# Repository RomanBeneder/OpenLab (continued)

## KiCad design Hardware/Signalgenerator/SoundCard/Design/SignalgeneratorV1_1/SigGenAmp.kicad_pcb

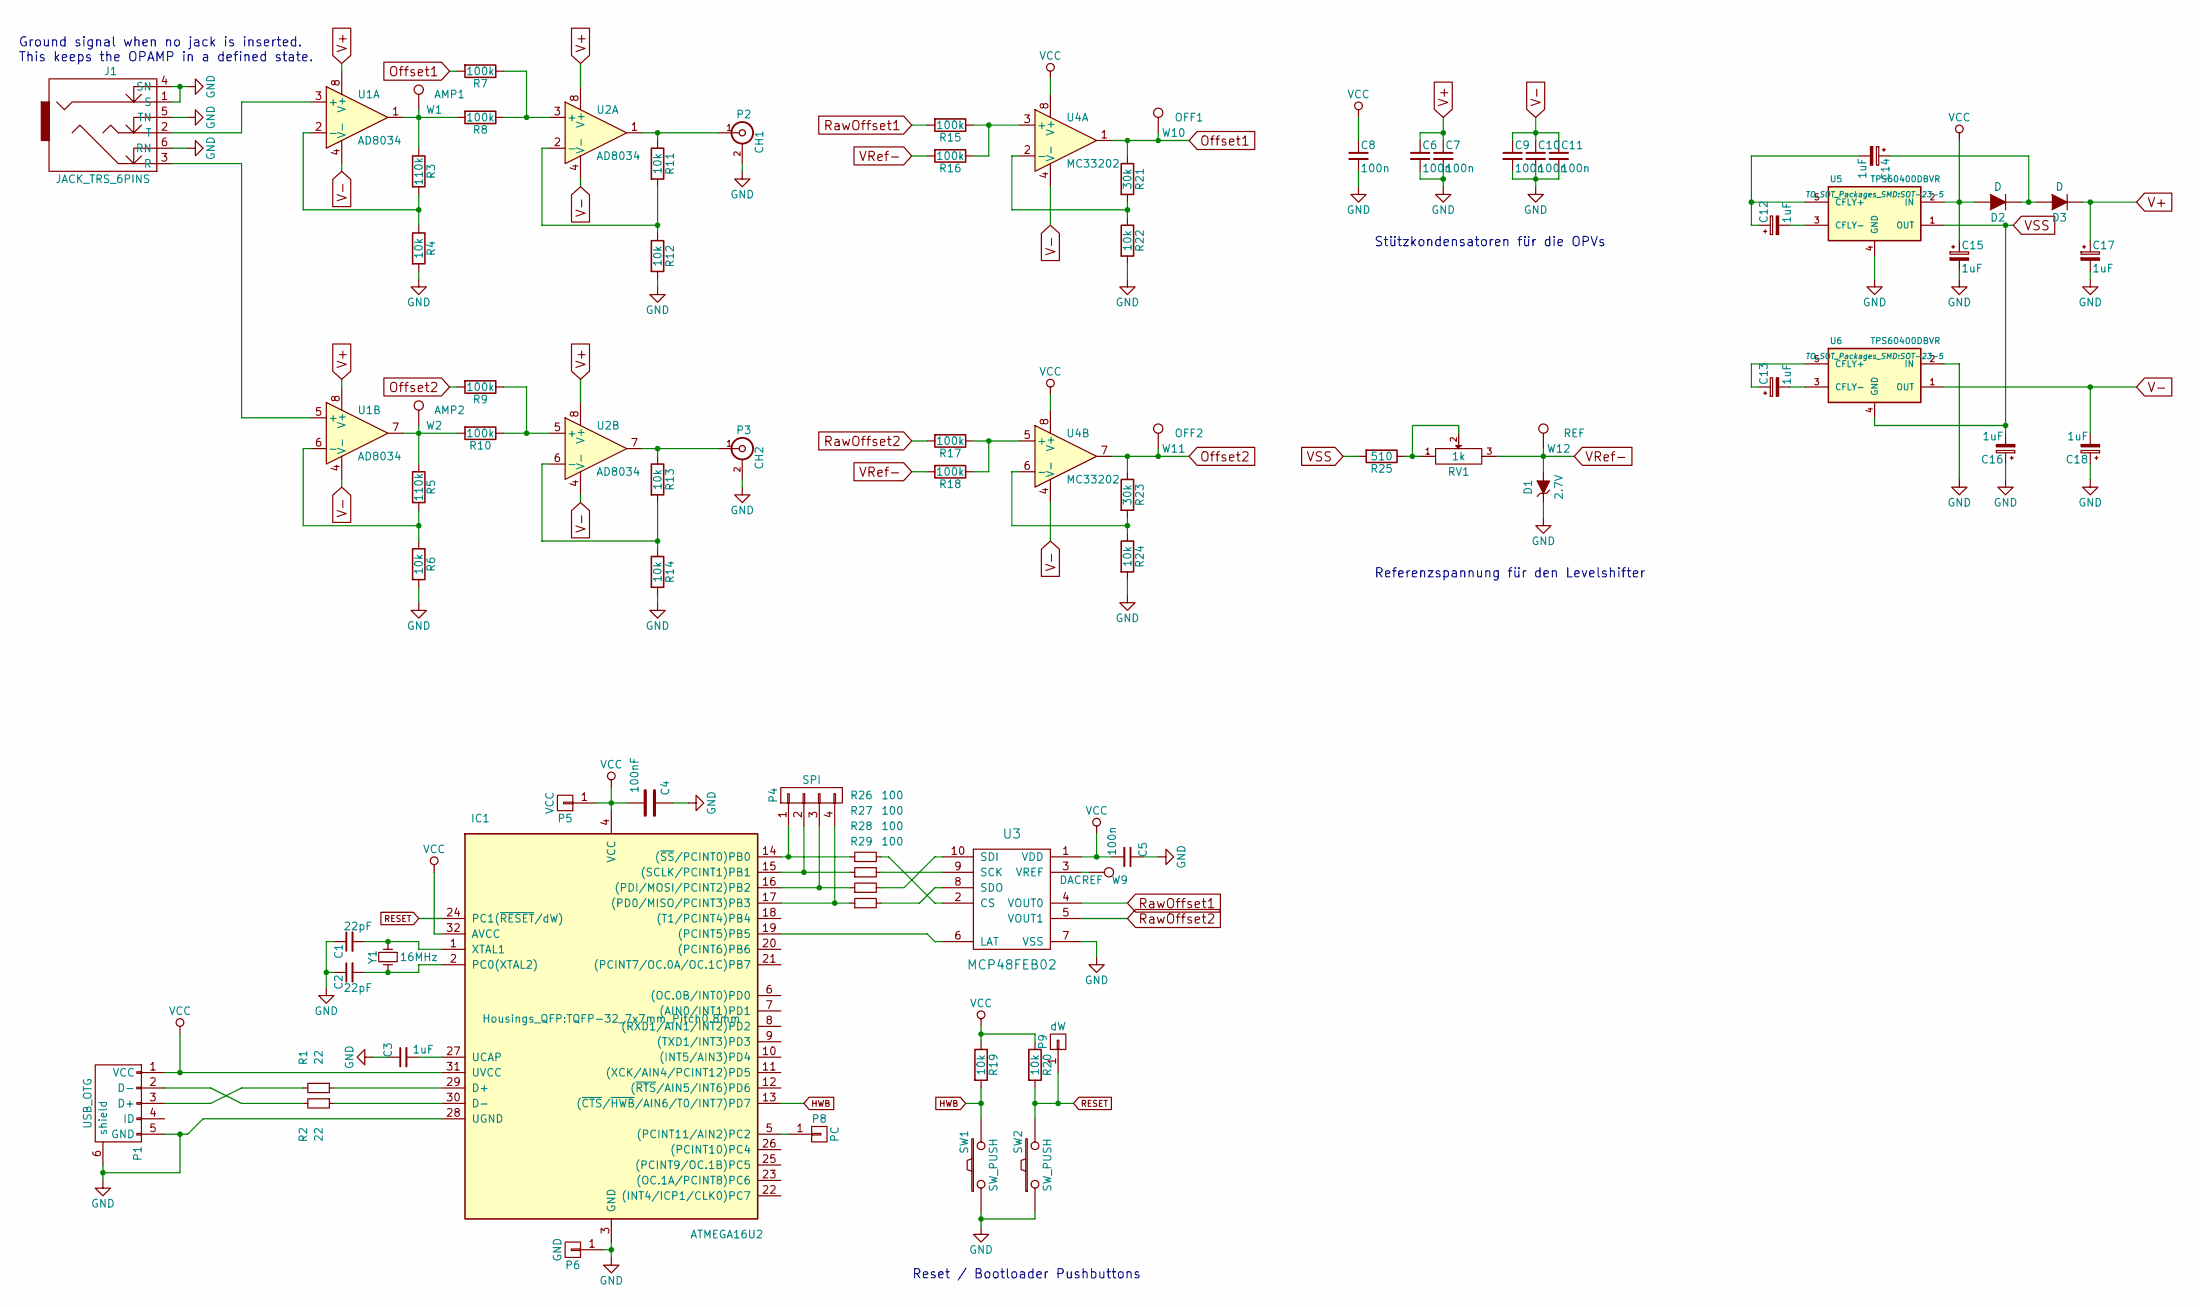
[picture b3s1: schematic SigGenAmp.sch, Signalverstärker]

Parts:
C1, C2: 22pF; C_0805_HandSoldering
C3, C12, C13, C14, C15, C16, C17, C18: 1uF; C_1206_HandSoldering
C4: 100nF; C_0805_HandSoldering
C5, C6, C7, C8, C9, C10, C11: 100n; C_0805_HandSoldering
D1: 2.7V; SOD-123
D2, D3: D; SOD-123
IC1: ATMEGA16U2; TQFP-32_7x7mm_Pitch0.8mm
J1: JACK_TRS_6PINS; TRS 3.5mm 5PIN
P1: USB_OTG; USB_Micro-B_SMD
P2: CH1; BNC_Socket_TYCO-AMP_FIX
P3: CH2; BNC_Socket_TYCO-AMP_FIX
P4: SPI; Pin_Header_Straight_1x04
P5: VCC; Pin_Header_Straight_1x01
P6: GND; Pin_Header_Straight_1x01
P8: PC; Pin_Header_Straight_1x01
P9: dW; Pin_Header_Straight_1x01
R1, R2: 22; R_0805_HandSoldering
R3, R5: 110k; R_0805_HandSoldering
R4, R6, R11, R12, R13, R14, R19, R20, R22, R24: 10k; R_0805_HandSoldering
R7, R8, R9, R10, R15, R16, R17, R18: 100k; R_0805_HandSoldering
R21, R23: 30k; R_0805_HandSoldering
R25: 510; R_0805_HandSoldering
R26, R27, R28, R29: 100; R_0805_HandSoldering
RV1: 1k; Potentiometer_Trimmer-EVM3E
SW1, SW2: SW_PUSH; SW_SPST_PTS645
U1, U2: AD8034; SOIC-8_3.9x4.9mm_Pitch1.27mm
U3: MCP48FEB02; MSOP-10_3x3mm_Pitch0.5mm
U4: MC33202; SOIC-8_3.9x4.9mm_Pitch1.27mm
U5, U6: TPS60400DBVR; SOT-23-5
W1: AMP1; Measurement_Point_Square-SMD-Pad_Small
W2: AMP2; Measurement_Point_Square-SMD-Pad_Small
W9: DACREF; Measurement_Point_Square-SMD-Pad_Small
W10: OFF1; Measurement_Point_Square-SMD-Pad_Small
W11: OFF2; Measurement_Point_Square-SMD-Pad_Small
W12: REF; Measurement_Point_Square-SMD-Pad_Small
Y1: 16MHz; Crystal_HC49-SD_SMD

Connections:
GND: C1.1, C2.1, C3.1, C4.1, C5.1, C6.2, C7.2, C8.2, C9.2, C10.2, C11.2, C15.2, C16.1, C17.2, C18.1, D1.1 (K), IC1.3 (GND), IC1.28 (UGND), J1.1 (S), J1.4 (SN), J1.5 (TN), J1.6 (RN), P1.5 (GND), P1.6 (shield), P2.2 (Ext), P3.2 (Ext), P6.1, R4.2, R6.2, R12.2, R14.2, R22.2, R24.2, SW1.1, SW2.1, U3.7 (VSS), U5.4 (GND), U6.2 (IN)
HWB: IC1.13 ((~CTS~/~HWB~/AIN6/T0/INT7)PD7), R19.2, SW1.2
unnamed: C1.2, IC1.1 (XTAL1), Y1.1
unnamed: C2.2, IC1.2 (PC0(XTAL2)), Y1.2
unnamed: C3.2, IC1.27 (UCAP)
unnamed: C12.1, C14.2, U5.5 (CFLY+)
unnamed: C12.2, U5.3 (CFLY-)
unnamed: C13.1, U6.5 (CFLY+)
unnamed: C13.2, U6.3 (CFLY-)
unnamed: C14.1, D2.1 (K), D3.2 (A)
unnamed: IC1.5 ((PCINT11/AIN2)PC2), P8.1
unnamed: IC1.14 ((~SS~/PCINT0)PB0), P4.1, R26.1
unnamed: IC1.15 ((SCLK/PCINT1)PB1), P4.2, R27.1
unnamed: IC1.16 ((PDI/MOSI/PCINT2)PB2), P4.3, R28.1
unnamed: IC1.17 ((PD0/MISO/PCINT3)PB3), P4.4, R29.1
unnamed: IC1.19 ((PCINT5)PB5), U3.6 (LAT)
unnamed: IC1.29 (D+), R1.1
unnamed: IC1.30 (D-), R2.1
unnamed: J1.2 (T), U1.3 (+)
unnamed: J1.3 (R), U1.5 (+)
unnamed: P1.2 (D-), R2.2
unnamed: P1.3 (D+), R1.2
unnamed: P2.1 (In), R11.1, U2.1
unnamed: P3.1 (In), R13.1, U2.7
unnamed: R3.1, R8.2, U1.1, W1.1
unnamed: R3.2, R4.1, U1.2 (-)
unnamed: R5.2, R6.1, U1.6 (-)
unnamed: R7.1, R8.1, U2.3 (+)
unnamed: R9.1, R10.1, U2.5 (+)
unnamed: R5.1, R10.2, U1.7, W2.1
unnamed: R11.2, R12.1, U2.2 (-)
unnamed: R13.2, R14.1, U2.6 (-)
unnamed: R15.1, R16.1, U4.3 (+)
unnamed: R17.1, R18.1, U4.5 (+)
unnamed: R21.2, R22.1, U4.2 (-)
unnamed: R23.2, R24.1, U4.6 (-)
unnamed: R25.1, RV1.1, RV1.2
unnamed: R26.2, U3.2 (CS)
unnamed: R27.2, U3.9 (SCK)
unnamed: R28.2, U3.10 (SDI)
unnamed: R29.2, U3.8 (SDO)
unnamed: U3.3 (VREF), W9.1
Offset1: R7.2, R21.1, U4.1, W10.1
Offset2: R9.2, R23.1, U4.7, W11.1
RESET: IC1.24 (PC1(~RESET~/dW)), P9.1, R20.2, SW2.2
RawOffset1: R15.2, U3.4 (VOUT0)
RawOffset2: R17.2, U3.5 (VOUT1)
V+: C6.1, C7.1, C17.1, D3.1 (K), U1.8 (V+), U2.8 (V+)
V-: C9.1, C10.1, C11.1, C18.2, U1.4 (V-), U2.4 (V-), U4.4 (V-), U6.1 (OUT)
VCC: C4.2, C5.2, C8.1, C15.1, D2.2 (A), IC1.4 (VCC), IC1.31 (UVCC), IC1.32 (AVCC), P1.1 (VCC), P5.1, R19.1, R20.1, U3.1 (VDD), U4.8 (V+), U5.2 (IN)
VRef-: D1.2 (A), R16.2, R18.2, RV1.3, W12.1
VSS: C16.2, R25.2, U5.1 (OUT), U6.4 (GND)

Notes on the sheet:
Stützkondensatoren für die OPVs
Referenzspannung für den Levelshifter
Reset / Bootloader Pushbuttons
Ground signal when no jack is inserted. This keeps the OPAMP in a defined state.

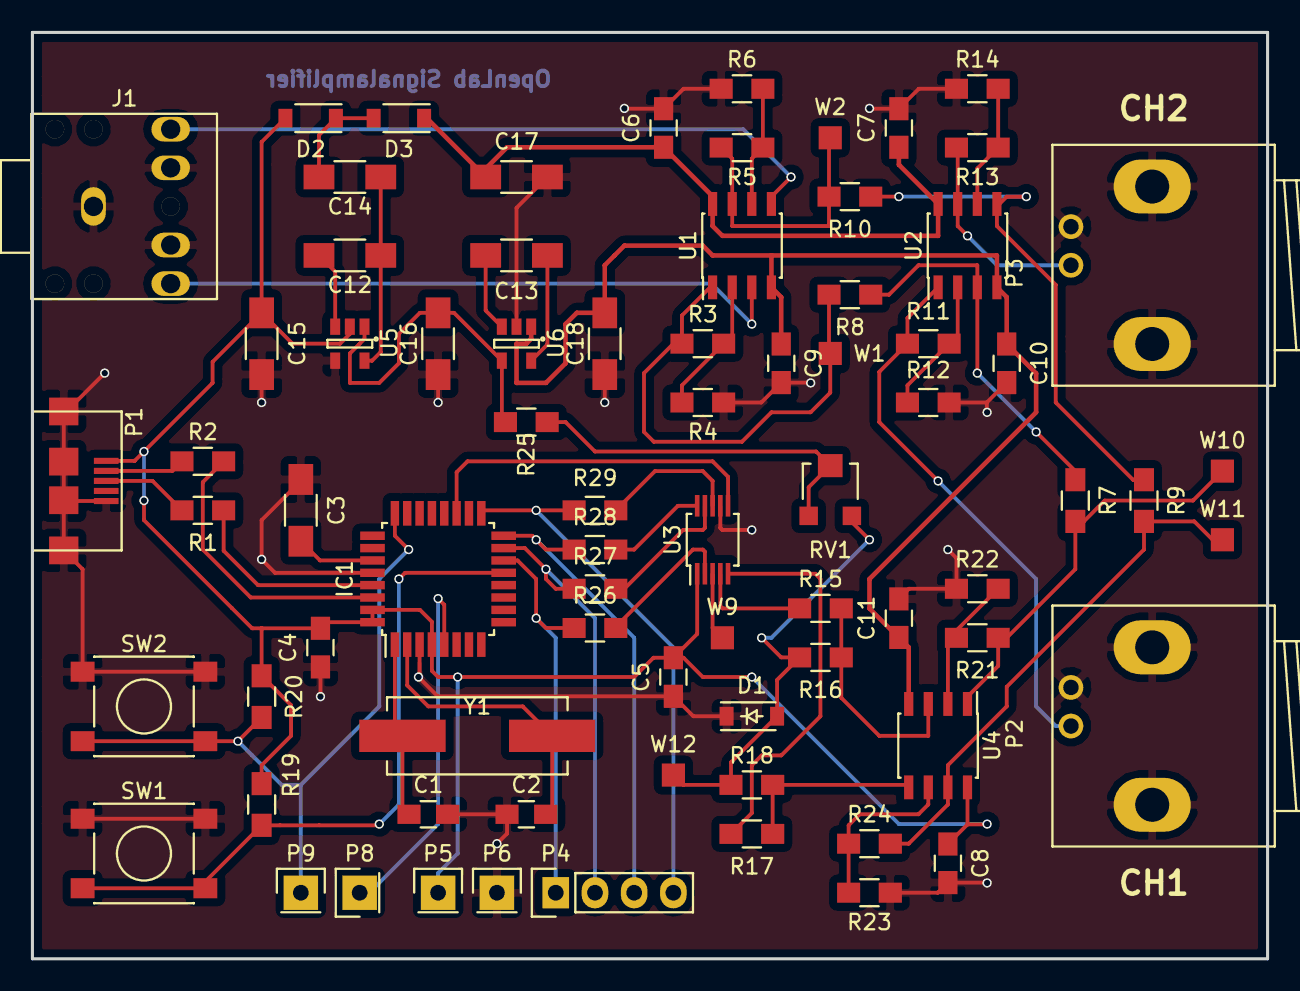
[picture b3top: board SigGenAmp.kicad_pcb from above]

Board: 4 copper layers, 80.0 x 60.0 mm, 76 parts (0 on the bottom side), 52 nets.
